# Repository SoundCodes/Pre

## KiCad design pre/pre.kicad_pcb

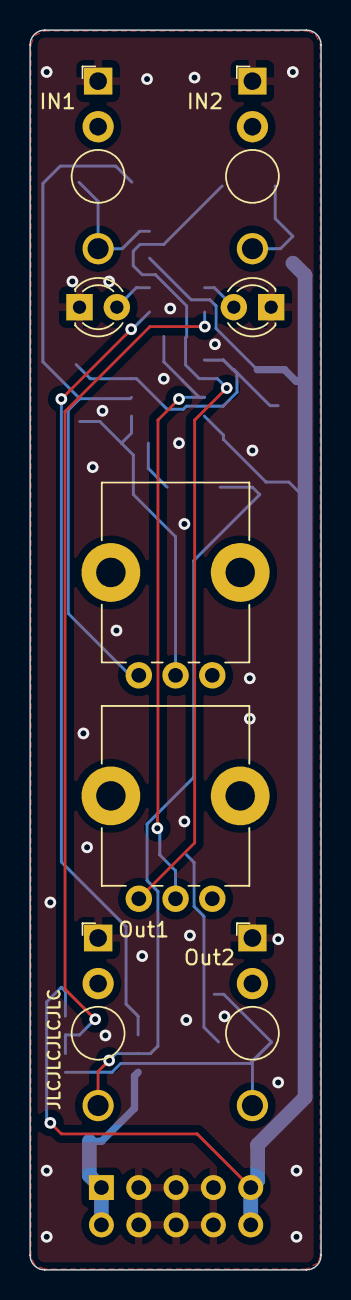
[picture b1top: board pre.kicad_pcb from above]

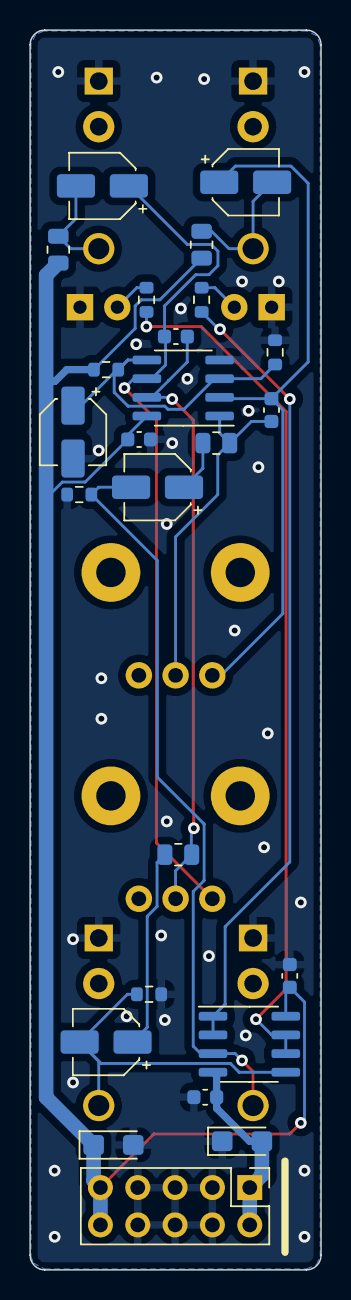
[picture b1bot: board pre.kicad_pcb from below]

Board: 2 copper layers, 19.8 x 84.3 mm, 35 parts (25 on the bottom side), 18 nets.

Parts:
C1, C2, C4, C5, C11: 2.2uF; CP_Elec_4x5.4
C3, C6: 15pF; C_0603_1608Metric
C7, C8, C10: 100nf; C_0603_1608Metric
C9, C12: 10uf; CP_EIA-3216-18_Kemet-A
IN1: In1; Jack_3.5mm_QingPu_WQP-PJ398SM_Vertical_CircularHoles
IN2: In2; Jack_3.5mm_QingPu_WQP-PJ398SM_Vertical_CircularHoles
J5: Conn_02x05_Odd_Even; PinHeader_2x05_P2.54mm_Vertical
LED1, LED2: LED; LED_D3.0mm
Out1: Out1; Jack_3.5mm_QingPu_WQP-PJ398SM_Vertical_CircularHoles
Out2: Out2; Jack_3.5mm_QingPu_WQP-PJ398SM_Vertical_CircularHoles
R1, R5: 20k; R_0805_2012Metric
R2, R6: 51; R_0805_2012Metric
R3, R7, R9, R10: 100k; R_0603_1608Metric
R4, R8: 1k; R_0603_1608Metric
RV1: In1_Gain; Potentiometer_Alps_RK09K_Single_Vertical
RV2: In2_Gain; Potentiometer_Alps_RK09K_Single_Vertical
U1, U2: TL072; SOIC-8_3.9x4.9mm_P1.27mm
svg2mod: G***; pre-bm
svg2mod#2: G***; soundcodes-logo-bm

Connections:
+12V: C7.2, C10.2, C12.1, J5.9, J5.10, R1.1, R5.1, R9.1, U1.8 (V+), U2.8 (V+)
-12V: C8.1, C9.2, J5.1, J5.2, U2.4 (V-)
GND: C7.1, C8.2, C9.1, C10.1, C11.2, C12.2, IN1.S, IN2.S, J5.3, J5.4, J5.5, J5.6, J5.7, J5.8, LED1.1 (K), LED2.1 (K), Out1.S, Out2.S, R3.2, R7.2, R10.2, U1.4 (V-)
unnamed: C1.1, R2.2
unnamed: C1.2, Out1.T, R3.1, U2.3 (+)
unnamed: C2.2, IN1.T, R1.2
unnamed: C4.1, R6.1
unnamed: C4.2, Out2.T, R7.1, U2.5 (+)
unnamed: C5.2, IN2.T, R5.2
unnamed: LED1.2 (A), R4.1
unnamed: LED2.2 (A), R8.1
unnamed: R4.2, U2.1, U2.2 (-)
unnamed: R8.2, U2.6 (-), U2.7
pot_a_L: C2.1, C3.2, RV1.3, U1.2 (-)
pot_a_R: C5.1, C6.2, RV2.3, U1.6 (-)
pot_b_L: C3.1, R2.1, RV1.2, U1.1
pot_b_R: C6.1, R6.2, RV2.2, U1.7
vgnd: C11.1, R9.2, R10.1, U1.3 (+), U1.5 (+)

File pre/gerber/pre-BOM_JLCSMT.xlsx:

Comment | Designator | Footprint | JLCPCB Part #（optional）
100k | R7,R9,R10,R3 | R_0603_1608Metric | C25803
100nf | C7,C8,C10 | C_0603_1608Metric | C14663
20k | R5,R1 | R_0805_2012Metric | C4328
TL072 | U1,U2 | SOIC-8_3.9x4.9mm_P1.27mm | C6961
10uf | C9,C12 | CP_EIA-3216-18_Kemet-A | C7171
15pF | C3,C6 | C_0603_1608Metric | C1644
2.2uF | C5,C2,C4,C1,C11 | CP_Elec_4x5.4 | C134236
1k | R8,R4 | R_0603_1608Metric | C21190
51 | R2,R6 | R_0805_2012Metric | C17738

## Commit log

2022-01-11 first
2022-01-12 v1
    First Order with JLC
2022-01-13 Alignment Fix
